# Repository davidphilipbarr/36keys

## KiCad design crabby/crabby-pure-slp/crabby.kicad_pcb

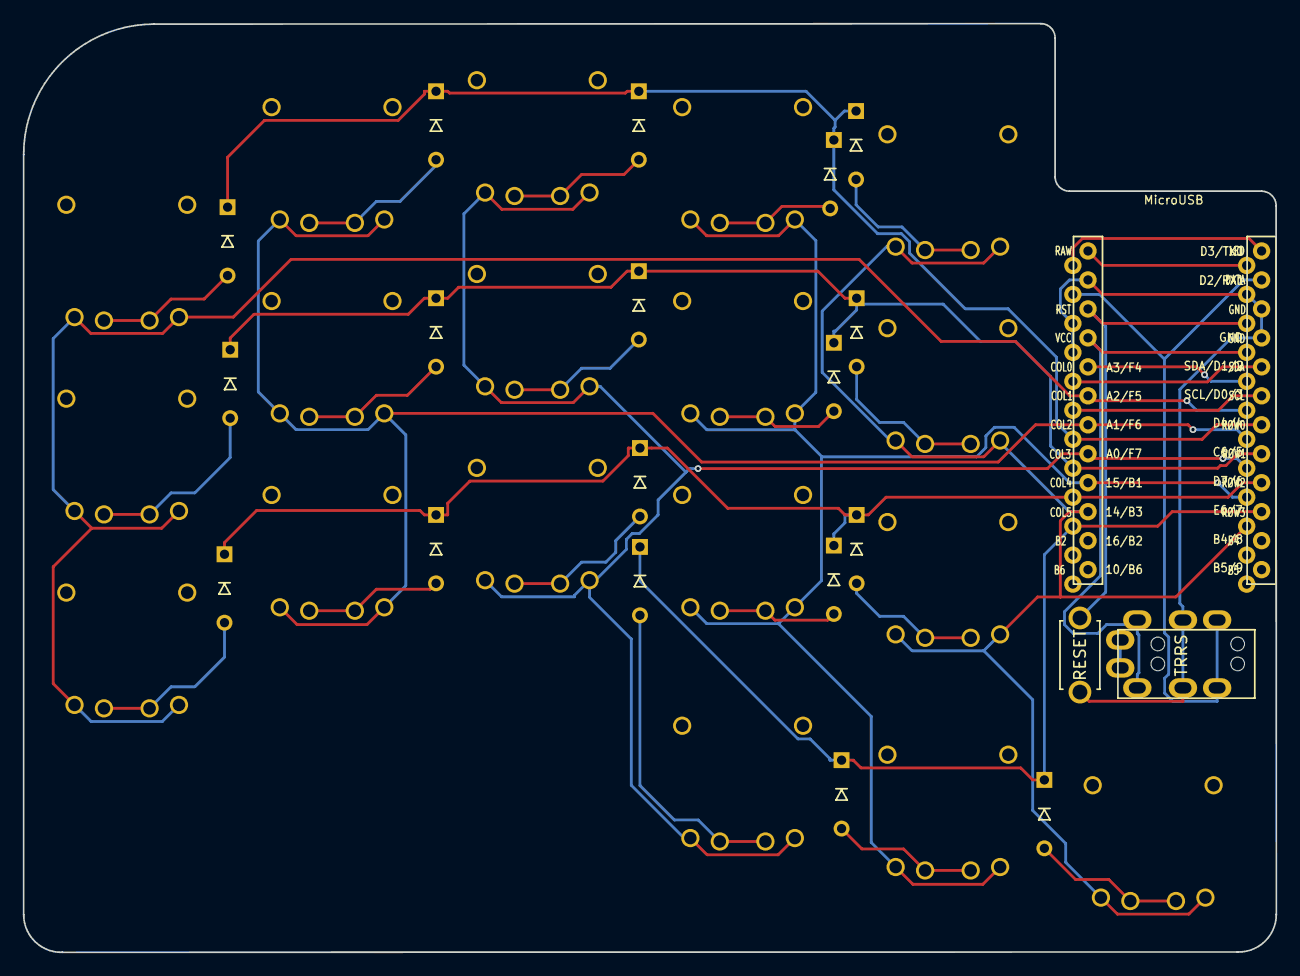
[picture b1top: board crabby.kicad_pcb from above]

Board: 2 copper layers, 109.8 x 81.4 mm, 39 parts (0 on the bottom side), 31 nets.

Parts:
D2, D3, D4, D5, D6, D8, D9, D10, D11, D12, D14, D15, D16, D17, D18, D19, D20, D21: D; D3_TH
J1: MJ-4PP-9
RSW1: Val**; ResetSW
SW2, SW3, SW4, SW5, SW6, SW8, SW9, SW10, SW11, SW12, SW14, SW15, SW16, SW17, SW18, SW19, SW20, SW21: SW_PUSH; Kailh_PG1232
U1: ProMicro; ProMicro_v2

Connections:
GND: J1.C, RSW1.2, U1.3, U1.4, U1.23
unnamed: D2.2, SW2.2
unnamed: D3.2, SW3.2
unnamed: D4.2, SW4.2
unnamed: D5.2, SW5.2
unnamed: D6.2, SW6.2
unnamed: D8.2, SW8.2
unnamed: D9.2, SW9.2
unnamed: D10.2, SW10.2
unnamed: D11.2, SW11.2
unnamed: D12.2, SW12.2
unnamed: D14.2, SW14.2
unnamed: D15.2, SW15.2
unnamed: D16.2, SW16.2
unnamed: D17.2, SW17.2
unnamed: D18.2, SW18.2
unnamed: D19.2, SW19.2
unnamed: D20.2, SW20.2
unnamed: D21.2, SW21.2
VCC: J1.D, U1.21
col1: SW2.1, SW8.1, SW14.1, U1.19
col2: SW3.1, SW9.1, SW15.1, U1.18
col3: SW4.1, SW10.1, SW16.1, SW19.1, U1.17
col4: SW5.1, SW11.1, SW17.1, SW20.1, U1.16
col5: SW6.1, SW12.1, SW18.1, SW21.1, U1.15
data: J1.B, U1.2
reset: RSW1.1, U1.22
row0: D2.1, D3.1, D4.1, D5.1, D6.1, U1.7
row1: D8.1, D9.1, D10.1, D11.1, D12.1, U1.8
row2: D14.1, D15.1, D16.1, D17.1, D18.1, U1.9
row3: D19.1, D20.1, D21.1, U1.10

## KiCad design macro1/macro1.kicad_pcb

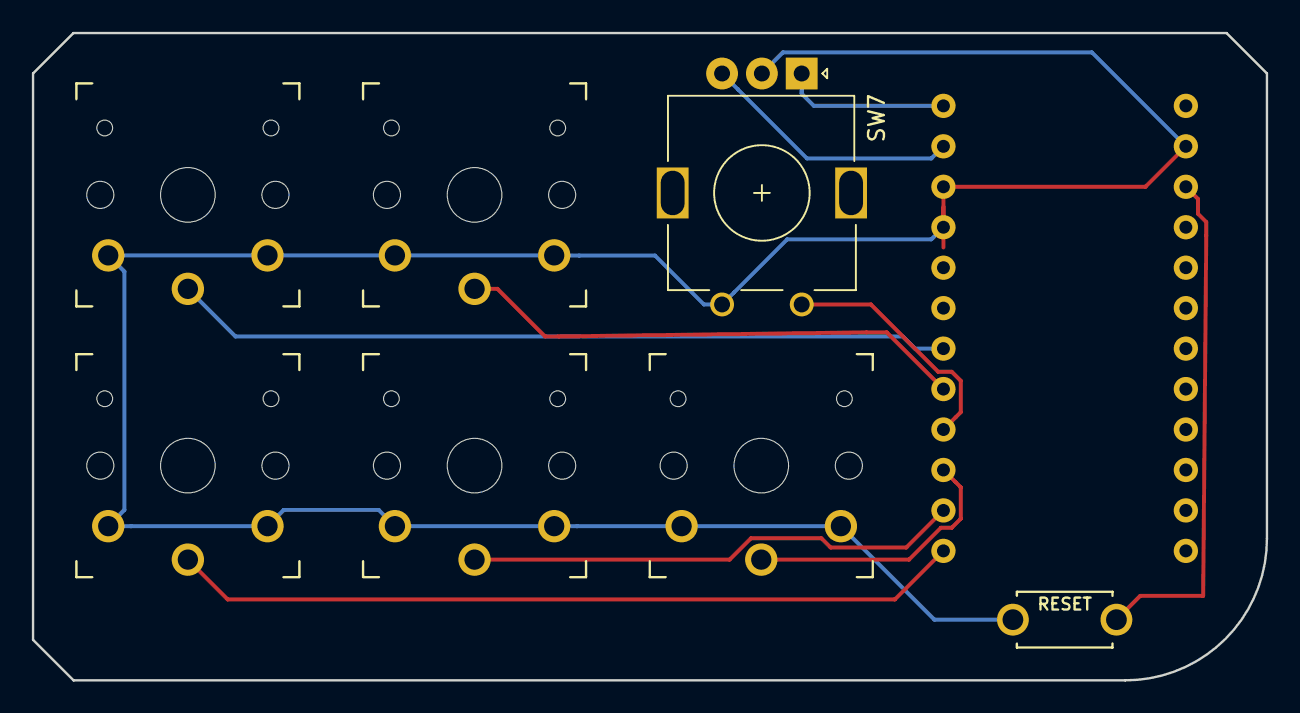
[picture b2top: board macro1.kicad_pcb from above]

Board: 2 copper layers, 77.5 x 40.6 mm, 8 parts (1 on the bottom side), 9 nets.

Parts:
RSW1: SW_Push; ResetSW_1side
SW1, SW2, SW4, SW5, SW6: SW_PUSH; SW_PG1350_reversible
SW7: Rotary_Encoder_Switch; RotaryEncoder_Alps_EC11E_Vertical_H20mm
U1: ProMicro_r; ProMicro_v3

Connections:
/RESET: RSW1.1, U1.22
/SW_1: SW1.1, U1.7
/SW_2: SW2.1, U1.8
/SW_4: SW4.1, U1.10
/SW_5: SW5.1, U1.11
/SW_6: SW6.1, U1.12
GND: RSW1.2, SW1.2, SW2.2, SW4.2, SW5.2, SW6.2, SW7.C, U1.3, U1.4, U1.23
unnamed: SW7.A, U1.1
unnamed: SW7.B, U1.2

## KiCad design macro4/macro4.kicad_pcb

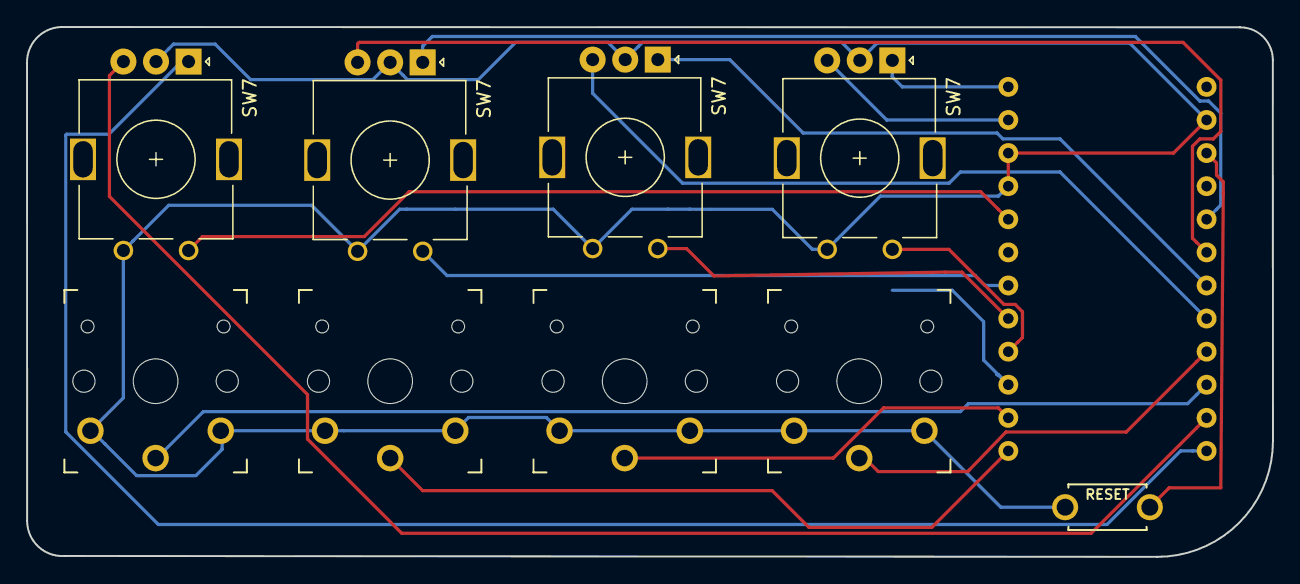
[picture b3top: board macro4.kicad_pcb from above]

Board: 2 copper layers, 95.6 x 40.7 mm, 10 parts (1 on the bottom side), 14 nets.

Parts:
RSW1: SW_Push; ResetSW_1side
SW2, SW5, SW6, SW8: SW_PUSH; SW_PG1350_reversible
SW7, SW7#2, SW7#3, SW7#4: Rotary_Encoder_Switch; RotaryEncoder_Alps_EC11E_Vertical_H20mm
U1: ProMicro_r; ProMicro_v3

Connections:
/RESET: RSW1.1, U1.22
/SW_5: SW5.1, U1.11
/SW_6: SW6.1, U1.12
GND: RSW1.2, SW2.2, SW5.2, SW6.2, SW7.C, SW7#2.C, SW7#3.C, SW7#4.C, SW8.2, U1.3, U1.4, U1.23
unnamed: SW7#4.A, U1.1
unnamed: SW7#4.B, U1.2
unnamed: SW7.A, U1.13
unnamed: SW7.B, U1.14
unnamed: SW8.1, U1.15
unnamed: SW2.1, U1.16
unnamed: SW7#3.B, U1.17
unnamed: SW7#3.A, U1.18
unnamed: SW7#2.B, U1.19
unnamed: SW7#2.A, U1.20

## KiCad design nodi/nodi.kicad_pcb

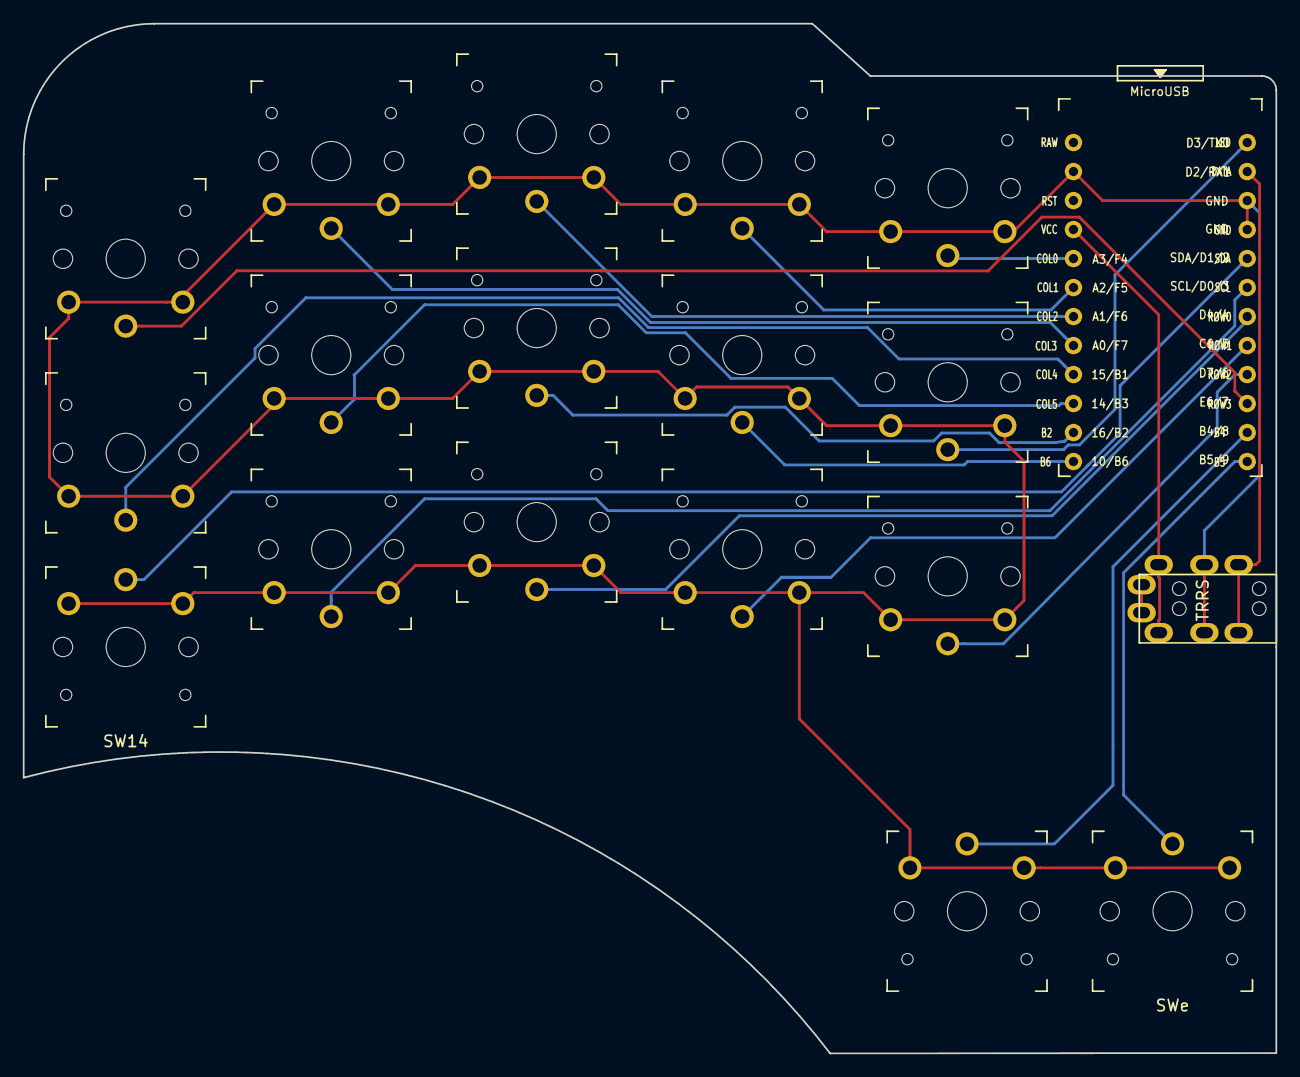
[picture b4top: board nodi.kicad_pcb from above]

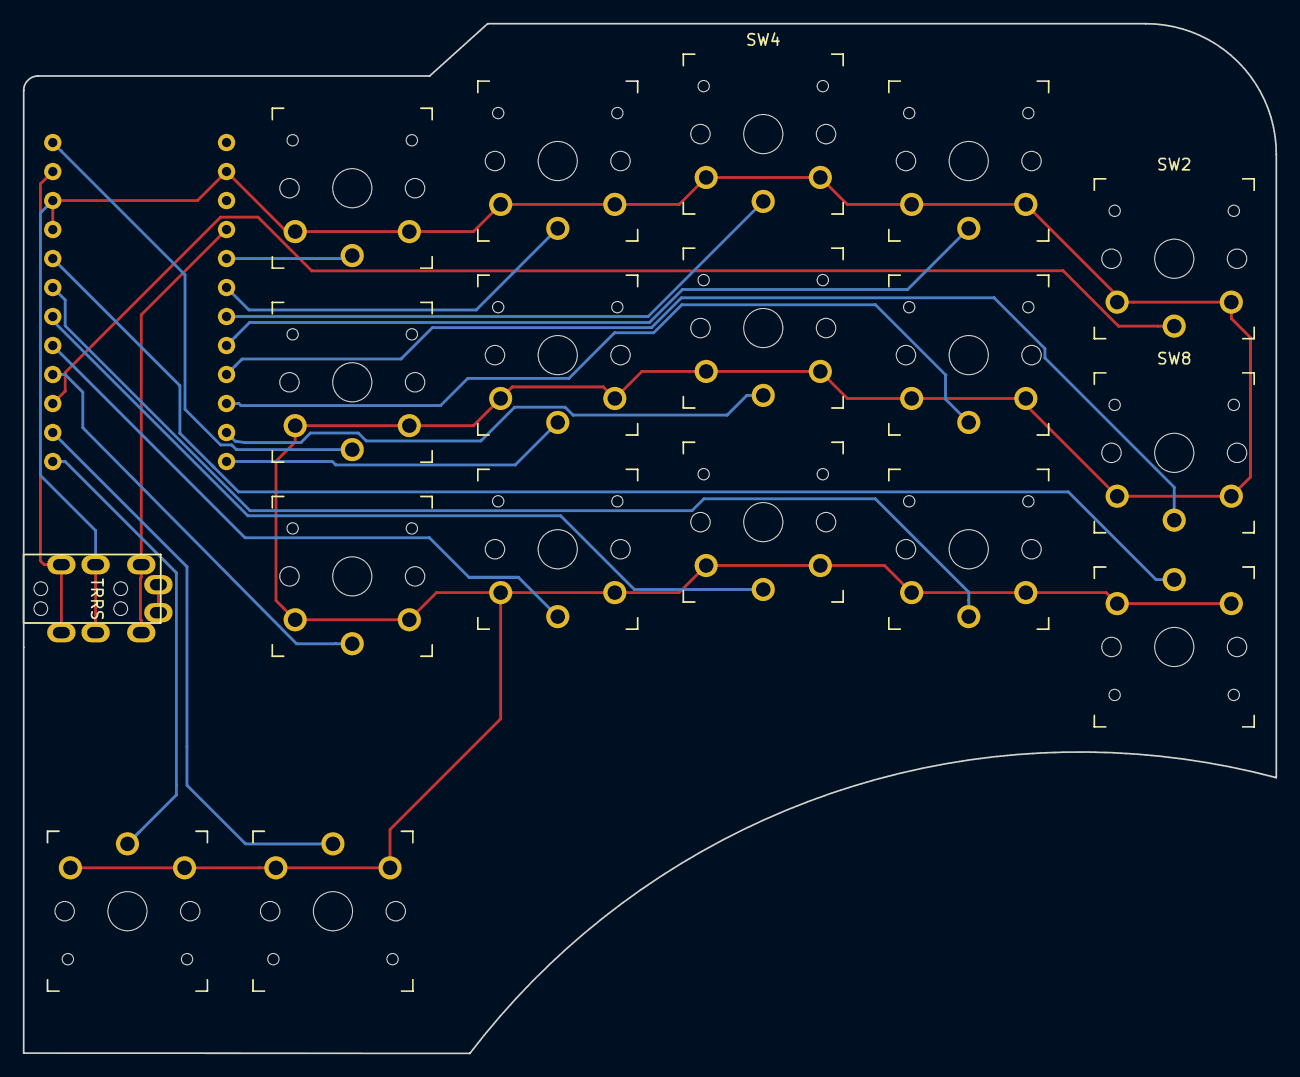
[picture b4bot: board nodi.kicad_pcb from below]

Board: 2 copper layers, 109.7 x 90.2 mm, 19 parts (3 on the bottom side), 20 nets.

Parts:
J1: MJ-4PP-9
SW2, SW3, SW4, SW5, SW6, SW8, SW9, SW10, SW11, SW12, SW14, SW15, SW16, SW17, SW18, SW20: SW_PUSH; SW_PG1350_reversible
SWe: SW_PUSH; SW_PG1350_reversible
U1: ProMicro; ProMicro_v3

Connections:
GND: J1.C, SW2.2, SW3.2, SW4.2, SW5.2, SW6.2, SW8.2, SW9.2, SW10.2, SW11.2, SW12.2, SW14.2, SW15.2, SW16.2, SW17.2, SW18.2, SW20.2, SWe.2, U1.3, U1.4, U1.23
LED: SW12.1, U1.1
unnamed: SW6.1, U1.20
unnamed: SW20.1, U1.11
unnamed: SWe.1, U1.12
unnamed: SW11.1, U1.13
unnamed: SW10.1, U1.14
SCL: SW15.1, U1.6
SDA: SW14.1, U1.5
VCC: J1.D, U1.21
col1: SW5.1, U1.19
col2: SW4.1, U1.18
col3: SW3.1, U1.17
col4: SW8.1, U1.16
col5: SW9.1, U1.15
data: J1.B, U1.2
row0: SW16.1, U1.7
row1: SW17.1, U1.8
row2: SW18.1, U1.9
row3: SW2.1, U1.10
